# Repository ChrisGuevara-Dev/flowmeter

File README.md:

# Flowmeter
The project focuses on developing a flow control system using a YF-S201 flow sensor and an electrovalve, both managed by an Atmega328P microcontroller. Through electronic design in KiCAD, precise arrangement of components and connections, as well as an optimal configuration of the printed circuit board (PCB) are planned. The primary focus of the project is to monitor and control the flow, with potential applications in irrigation systems.

## Schematic

## 3D Model & Implementation

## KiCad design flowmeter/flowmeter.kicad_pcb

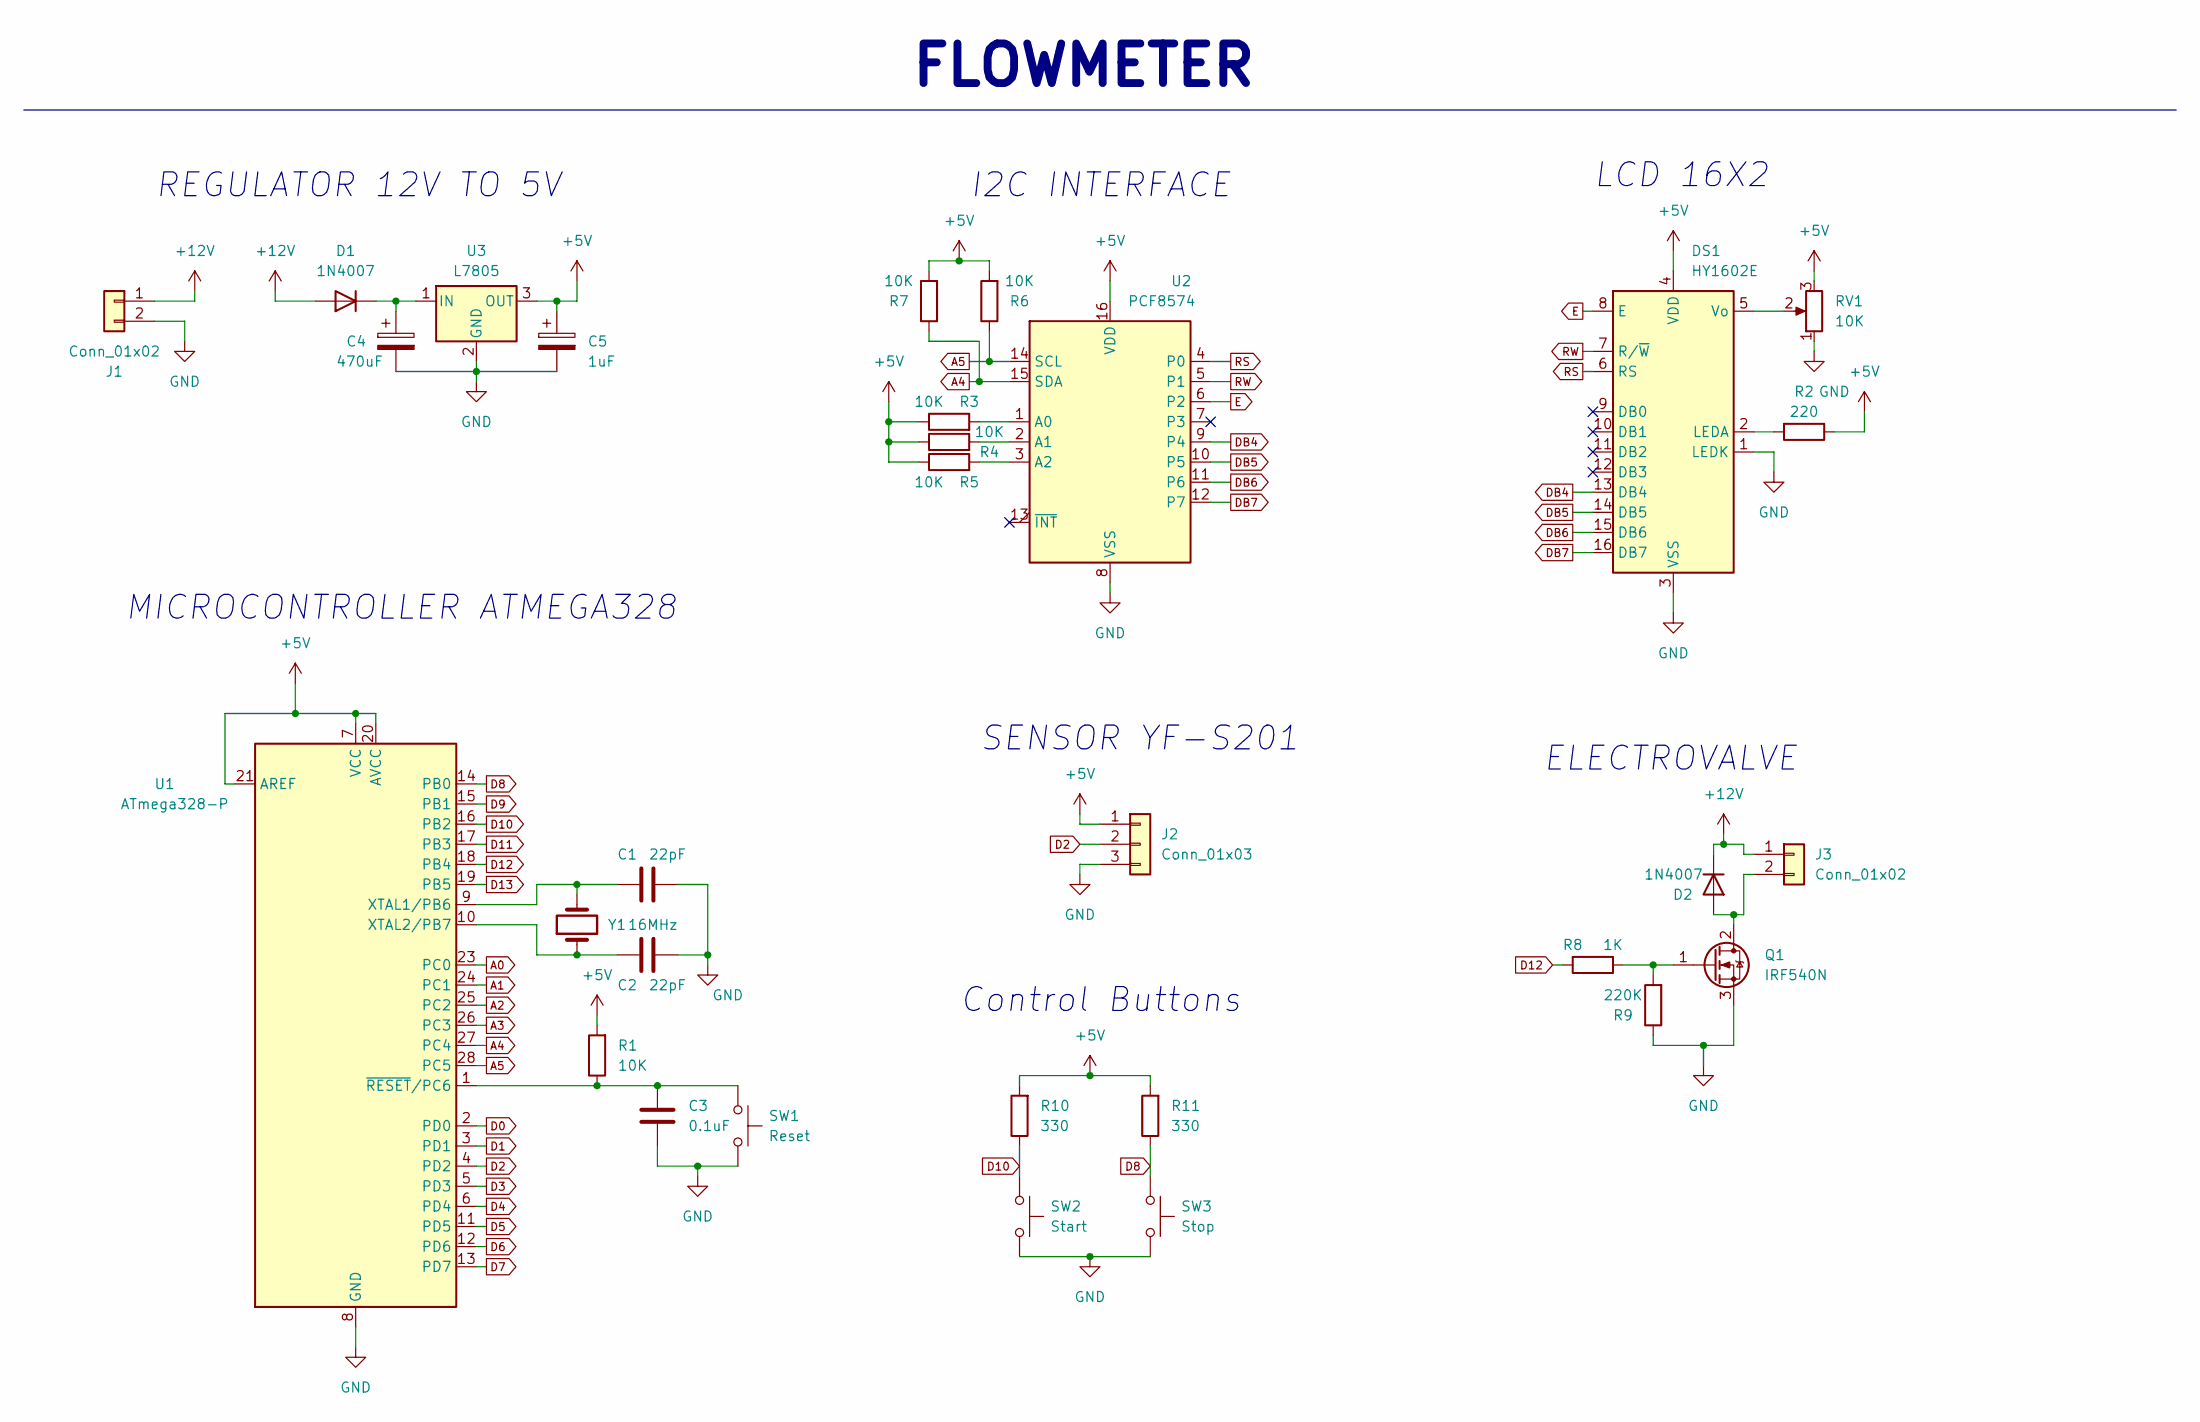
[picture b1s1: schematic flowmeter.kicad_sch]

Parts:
C1, C2: 22pF; C_0805_2012Metric
C3: 0.1uF; C_0805_2012Metric
C4: 470uF; CP_Elec_5x5.8
C5: 1uF; CP_Elec_5x5.8
D1, D2: 1N4007; D_DO-41_SOD81_P10.16mm_Horizontal
DS1: HY1602E
J1, J3: Conn_01x02; TerminalBlock_Phoenix_MKDS-1,5-2-5.08_1x02_P5.08mm_Horizont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
J2: Conn_01x03; PhoenixContact_MSTBA_2,5_3-G-5,08_1x03_P5.08mm_Horizontal
Q1: IRF540N; TO-220-3_Vertical
R1, R3, R4, R5, R6, R7: 10K; R_0805_2012Metric
R2: 220; R_0805_2012Metric
R8: 1K; R_0805_2012Metric
R9: 220K; R_0805_2012Metric
R10, R11: 330; R_0805_2012Metric
RV1: 10K; TC33X2503E
SW1: Reset; LL3301FF065QJ
SW2: Start; LL3301FF065QJ
SW3: Stop; LL3301FF065QJ
U1: ATmega328-P; DIP-28_W7.62mm
U2: PCF8574; TSSOP-20_4.4x6.5mm_P0.65mm
U3: L7805; TO-220-3_Vertical
Y1: 16MHz; Crystal_HC49-4H_Vertical

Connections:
+5V: C5.1, DS1.4 (VDD), J2.1, R1.2, R2.1, R3.1, R4.1, R5.1, R6.2, R7.2, R10.2, R11.2, RV1.3, U1.7 (VCC), U1.20 (AVCC), U1.21 (AREF), U2.16 (VDD), U3.3 (OUT)
+12V: D1.2 (A), D2.1 (K), J1.1, J3.1
A0: U1.23 (PC0)
A1: U1.24 (PC1)
A2: U1.25 (PC2)
A3: U1.26 (PC3)
A4: R7.1, U1.27 (PC4), U2.15 (SDA)
A5: R6.1, U1.28 (PC5), U2.14 (SCL)
D0: U1.2 (PD0)
D1: U1.3 (PD1)
D2: J2.2, U1.4 (PD2)
D3: U1.5 (PD3)
D4: U1.6 (PD4)
D5: U1.11 (PD5)
D6: U1.12 (PD6)
D7: U1.13 (PD7)
D8: R11.1, SW3.1, U1.14 (PB0)
D9: U1.15 (PB1)
D10: R10.1, SW2.1, U1.16 (PB2)
D11: U1.17 (PB3)
D12: R8.2, U1.18 (PB4)
D13: U1.19 (PB5)
DB4: DS1.13 (DB4), U2.9 (P4)
DB5: DS1.14 (DB5), U2.10 (P5)
DB6: DS1.15 (DB6), U2.11 (P6)
DB7: DS1.16 (DB7), U2.12 (P7)
E: DS1.8 (E), U2.6 (P2)
GND: C1.1, C2.1, C3.2, C4.2, C5.2, DS1.1 (LEDK), DS1.3 (VSS), J1.2, J2.3, Q1.3 (S), R9.1, RV1.1, SW1.2, SW2.2, SW3.2, U1.8 (GND), U1.22 (GND), U2.8 (VSS), U3.2 (GND)
unnamed: C4.1, D1.1 (K), U3.1 (IN)
unnamed: D2.2 (A), J3.2, Q1.2 (D)
unnamed: DS1.2 (LEDA), R2.2
unnamed: DS1.5 (Vo), RV1.2
unnamed: Q1.1 (G), R8.1, R9.2
unnamed: C1.2, U1.9 (XTAL1/PB6), Y1.2
unnamed: C2.2, U1.10 (XTAL2/PB7), Y1.1
unnamed: C3.1, R1.1, SW1.1, U1.1 (~RESET/PC6)
unnamed: R3.2, U2.1 (A0)
unnamed: R4.2, U2.2 (A1)
unnamed: R5.2, U2.3 (A2)
RS: DS1.6 (RS), U2.4 (P0)
RW: DS1.7 (R/~W), U2.5 (P1)

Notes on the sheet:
Control Buttons
REGULATOR 12V TO 5V
SENSOR YF-S201
I2C INTERFACE
LCD 16X2
MICROCONTROLLER ATMEGA328
FLOWMETER
ELECTROVALVE

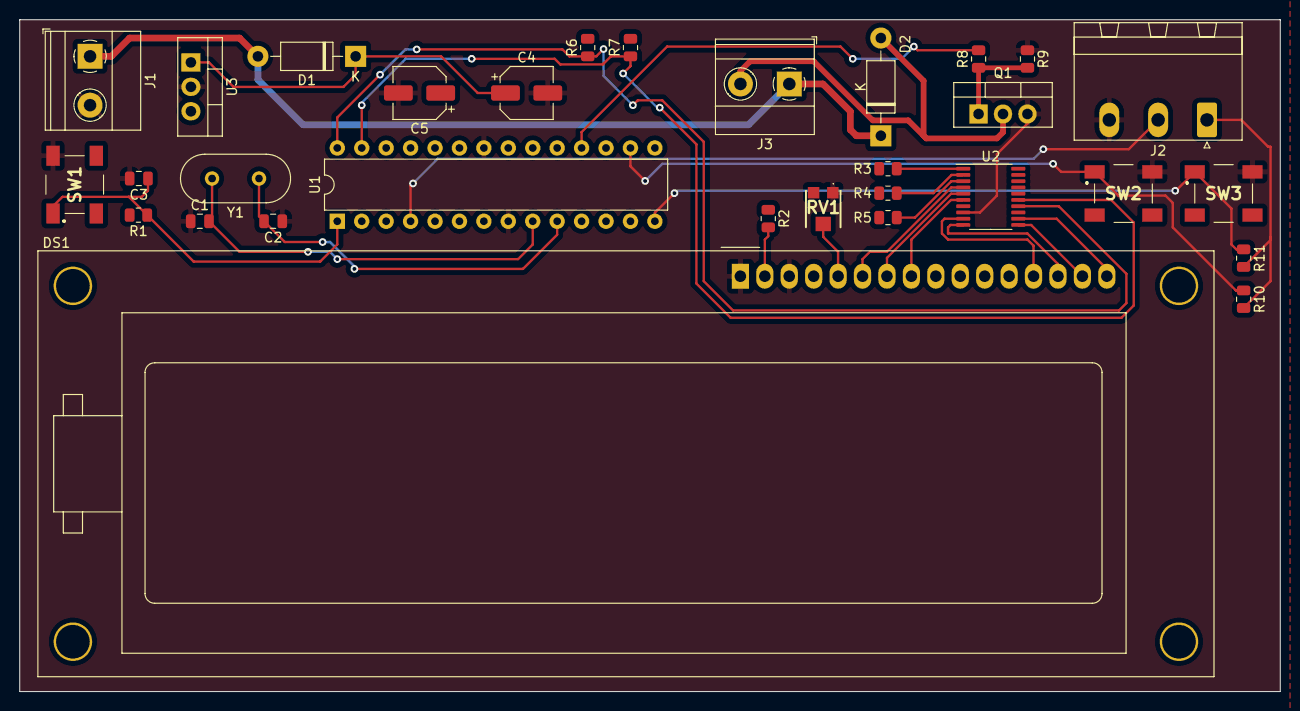
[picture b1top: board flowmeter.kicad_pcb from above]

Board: 2 copper layers, 131.1 x 69.9 mm, 31 parts (0 on the bottom side), 27 nets.
